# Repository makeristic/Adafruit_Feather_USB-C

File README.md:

# Adafruit Feather USB-C KiCad template

A KiCad project template for designing USB-C boards around the [Adafruit Feather specification](https://learn.adafruit.com/adafruit-feather/feather-specification). It includes the board outline, mounting holes, 12-pin and 16-pin headers, a USB-C receptacle, and a two-pin JST PH battery connector.

## Status

This is a starting layout, with no routed PCB tracks. USB-C VBUS and ground are assigned in the schematic, while USB data and CC connections remain unconnected. Add the required USB-C termination, power circuitry, controller, and application circuit before fabrication. The checked-in PCB was saved by KiCad 5.1.6; its legacy schematic and project formats are retained. The [correctness audit](docs/code-audit-report.md) confirms schematic/PCB connector-net agreement and records remaining ERC, DRC, and mounting-hole concerns. It does not establish electrical or manufacturing validation.

## Use the template

```sh
git clone https://github.com/makeristic/Adafruit_Feather_USB-C.git
```

1. Copy the `Adafruit_Feather_USB-C` directory, including `meta/`, into your KiCad user templates directory. The archived [KiCad 5.1 template-location documentation](https://docs.kicad.org/5.1/en/kicad/kicad.html#template_locations) describes the directory layout.
2. In KiCad, create a project from a template and select this template under User Templates. Alternatively, open [Adafruit_Feather_USB-C.pro](Adafruit_Feather_USB-C.pro) to inspect the source.
3. Install KiCad's standard symbol, footprint, and 3D-model libraries. The source uses standard `Connector`, `Connector_Generic`, and `power` symbols and connector footprints. Retain the supplied `-cache.lib`: it contains the original `USB_C_Receptacle_USB2.0` symbol, which is absent under that name in current libraries. Models reference `${KISYS3DMOD}`; when using a newer release, check that this legacy path variable points to your installed 3D-model directory and resolve any changed model filenames.
4. Work in a copy when opening with a newer KiCad release, which may convert the legacy files. Review the Feather pinout, connector orientation, and all USB-C and power connections, then run ERC and DRC on your completed design.

The schematic identifies USB-C connector `U262-161N-4BVC11` (LCSC `C319148`) and battery connector `S2B-PH-SM4-TB(LF)(SN)` (LCSC `C295747`). Verify the selected parts against their current datasheets before ordering.

## Files

- [Adafruit_Feather_USB-C.sch](Adafruit_Feather_USB-C.sch): legacy schematic with connector pin labels and connector part numbers.
- [Adafruit_Feather_USB-C.kicad_pcb](Adafruit_Feather_USB-C.kicad_pcb): board outline and placed footprints.
- [Adafruit_Feather_USB-C-cache.lib](Adafruit_Feather_USB-C-cache.lib): cached schematic symbols.
- [meta/](meta/): KiCad template description, icon, and board preview.

No firmware, BOM export, or Gerber fabrication package is included.

## Related projects and contributions

Use [Adafruit_Feather](https://github.com/makeristic/Adafruit_Feather) for the original Micro-USB variant. [Feather_STM32WB55](https://github.com/makeristic/Feather_STM32WB55) is a separate STM32WB55 board design; [Makeristic-KiCad-Library](https://github.com/makeristic/Makeristic-KiCad-Library) contains additional parts and a USB-C connector model.

Report problems through [GitHub issues](https://github.com/makeristic/Adafruit_Feather_USB-C/issues), including your KiCad version and any missing-library messages. For layout changes, include schematic or board screenshots and explain any change to Feather compatibility.

## Attribution and licence

Original template copyright © 2019 [arturo182](https://twitter.com/arturo182), from [KiCad/kicad-templates pull request #23](https://github.com/KiCad/kicad-templates/pull/23/files#diff-a7a7ac8a622f8aa19b54fb2f3cf42329). Michael Cutler adapted the template for USB-C in 2020; the original attribution remains in the template metadata.

The [upstream licence at the source revision](https://github.com/KiCad/kicad-templates/blob/459d6bc93c55cfdac9f9b5d629b44cb891b5f2b8/LICENSE.md) is Creative Commons Attribution-ShareAlike 4.0 with the KiCad library exception. A copy is included in [LICENSE.md](LICENSE.md). The derived template has not been relicensed to MIT; consult the licence for the distinction between using library data in a design and redistributing the template collection.

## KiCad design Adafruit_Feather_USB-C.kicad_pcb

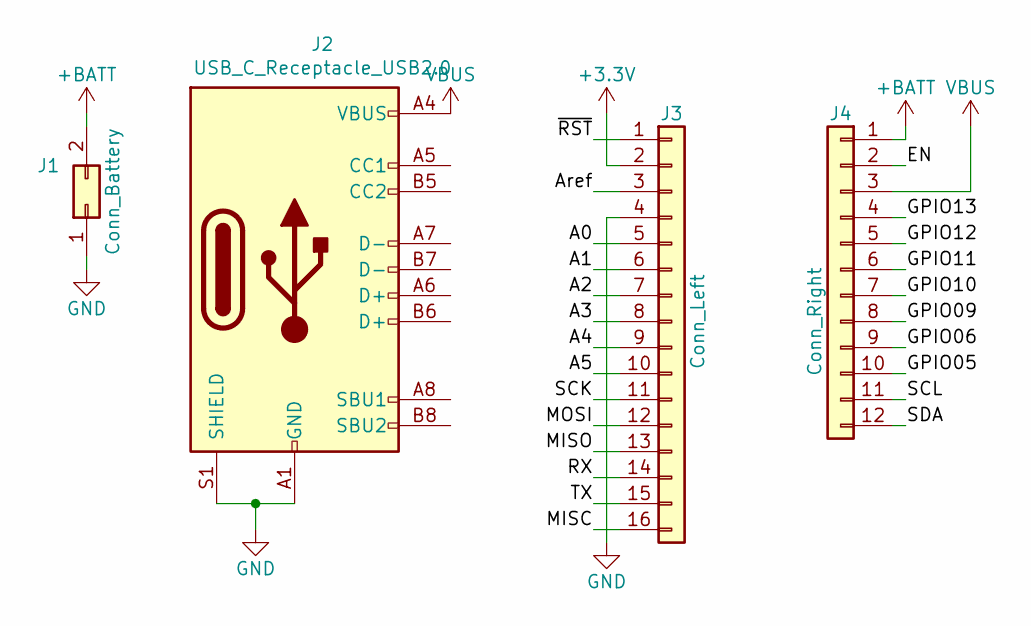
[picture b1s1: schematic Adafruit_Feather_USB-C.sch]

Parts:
J1: Conn_Battery; JST_PH_S2B-PH-SM4-TB_1x02-1MP_P2.00mm_Horizontal
J2: USB_C_Receptacle_USB2.0; USB_C_Receptacle_XKB_U262-16XN-4BVC11
J3: Conn_Left; PinHeader_1x16_P2.54mm_Vertical
J4: Conn_Right; PinHeader_1x12_P2.54mm_Vertical

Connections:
+3V3: J3.2
+BATT: J1.2, J4.1
/A0: J3.5
/A1: J3.6
/A2: J3.7
/A3: J3.8
/A4: J3.9
/A5: J3.10
/Aref: J3.3
/EN: J4.2
/GPIO05: J4.10
/GPIO06: J4.9
/GPIO09: J4.8
/GPIO10: J4.7
/GPIO11: J4.6
/GPIO12: J4.5
/GPIO13: J4.4
/MISC: J3.16
/MISO: J3.13
/MOSI: J3.12
/RX: J3.14
/SCK: J3.11
/SCL: J4.11
/SDA: J4.12
/TX: J3.15
/~RST~: J3.1
GND: J1.1, J2.A1 (GND), J2.A12 (GND), J2.B1 (GND), J2.B12 (GND), J2.S1 (SHIELD), J3.4
VBUS: J2.A4 (VBUS), J2.A9 (VBUS), J2.B4 (VBUS), J2.B9 (VBUS), J4.3

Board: 2 copper layers, 4 parts (0 on the bottom side), 3 nets, no tracks yet.

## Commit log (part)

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2020-10-09 Updated the board image
2020-10-09 Added part numbers
2020-10-09 Removing bak files
